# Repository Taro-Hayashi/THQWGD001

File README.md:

# 1U Wheel Encoder THQWGD001 with Tatctile Button
([日本語（note）](https://note.com/taro_hayashi/n/nf608af2136d1))

## Files
- https://github.com/Taro-Hayashi/THQWGD001/tree/main/step/THQWGD001C

<p xmlns:cc="http://creativecommons.org/ns#" xmlns:dct="http://purl.org/dc/terms/"><a property="dct:title" rel="cc:attributionURL" href="https://github.com/Taro-Hayashi/THQWGD001">THQWGD001C</a> by <a rel="cc:attributionURL dct:creator" property="cc:attributionName" href="https://x.com/w_vwbw">Taro Hayashi</a> is licensed under <a href="https://creativecommons.org/licenses/by/4.0/?ref=chooser-v1" target="_blank" rel="license noopener noreferrer" style="display:inline-block;">CC BY 4.0</a></p>

## Required

||||
|-|-|-|
|Shaft|1|THQWGD001C_shaft.stp|
|Spacer|1|THQWGD001C_spacer.stp|
|Curve wheel|1|THQWGD001C_wheel_curve.stp|
|Flat wheel|1|THQWGD001C_wheel_flat.stp|
|Base|1|THQWGD001C_base.stp|
|Cover|1|THQWGD001C_cover.stp|
|[Wheel Encoder](https://ja.aliexpress.com/item/1005010195419235.html)|1|11mm|
|[Tactile Button](https://www.aliexpress.com/w/wholesale-B3F%2525252d1062.html)|1|6x6x7mm|
|M2 screws|2|5mm or 6mm|
|M2 nuts|2||

### Assemble guide

- https://github.com/Taro-Hayashi/THQWGD001/tree/main/assemble_c.md

## Footprints and Symbol

- https://github.com/Taro-Hayashi/THQWGD001/tree/main/KiCad/

# 1U Wheel Encoder THQWGD001

## Files

- GitHub https://github.com/Taro-Hayashi/THQWGD001/tree/main/step/THQWGD001
- Printables https://www.printables.com/model/949835-1u-wheel-encoder-thqwgd001
- Maker World https://makerworld.com/en/models/550355#profileId-468693

<p xmlns:cc="http://creativecommons.org/ns#" xmlns:dct="http://purl.org/dc/terms/"><a property="dct:title" rel="cc:attributionURL" href="https://github.com/Taro-Hayashi/THQWGD001">THQWGD001</a> by <a rel="cc:attributionURL dct:creator" property="cc:attributionName" href="https://x.com/w_vwbw">Taro Hayashi</a> is licensed under <a href="https://creativecommons.org/licenses/by/4.0/?ref=chooser-v1" target="_blank" rel="license noopener noreferrer" style="display:inline-block;">CC BY 4.0</a></p>

## Required

||||
|-|-|-|
|Curve wheel|1|THQWGD001_wheel_curve.stp|
|Flat wheel|1|THQWGD001_wheel_flat.stp|
|Shaft|1|THQWGD001_shaft.stp|
|Base|1|THQWGD001_base.stp|
|Cover|1|THQWGD001_cover.stp|
|[Wheel Encoder](https://www.aliexpress.com/item/1005005353854113.html)|1|11mm|
|M2 screws|2|5mm or 6mm|
|M2 nuts|2||

### Assemble guide
- https://github.com/Taro-Hayashi/THQWGD001/tree/main/assemble.md

## Footprints and Symbol
- https://github.com/Taro-Hayashi/THQWGD001/tree/main/KiCad/

# PCB Sample
- https://github.com/Taro-Hayashi/THQWGD001/tree/main/PCB_sample

# BOOTH
https://tarohayashi.booth.pm/items/5967252

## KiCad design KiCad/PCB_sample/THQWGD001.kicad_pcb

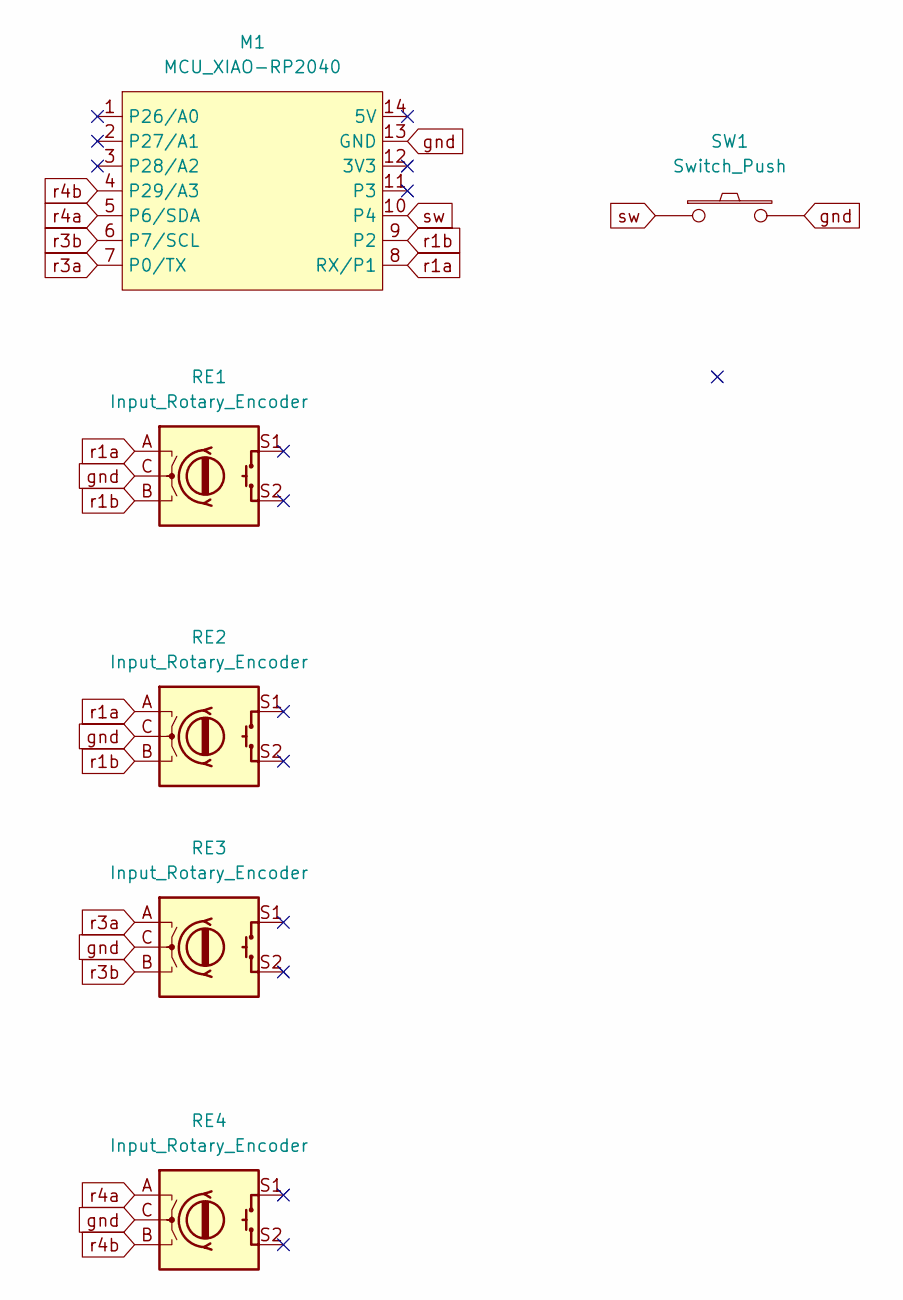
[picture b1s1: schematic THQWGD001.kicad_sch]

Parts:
M1: MCU_XIAO-RP2040; MCU_XIAO_RP2040
RE1, RE2, RE3: Input_Rotary_Encoder; THQWGD001
RE4: Input_Rotary_Encoder; THQWGD001_Reversible
SW1: Switch_Push; Switch_Cherry_MX_Socket 2

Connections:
gnd: M1.13 (GND), RE1.C, RE2.C, RE3.C, RE4.C, SW1.2
q: RE1.MP, RE2.MP
r1a: M1.8 (RX/P1), RE1.A, RE2.A
r1b: M1.9 (P2), RE1.B, RE2.B
r3a: M1.7 (P0/TX), RE3.A
r3b: M1.6 (P7/SCL), RE3.B
r4a: M1.5 (P6/SDA), RE4.A
r4b: M1.4 (P29/A3), RE4.B
sw: M1.10 (P4), SW1.1

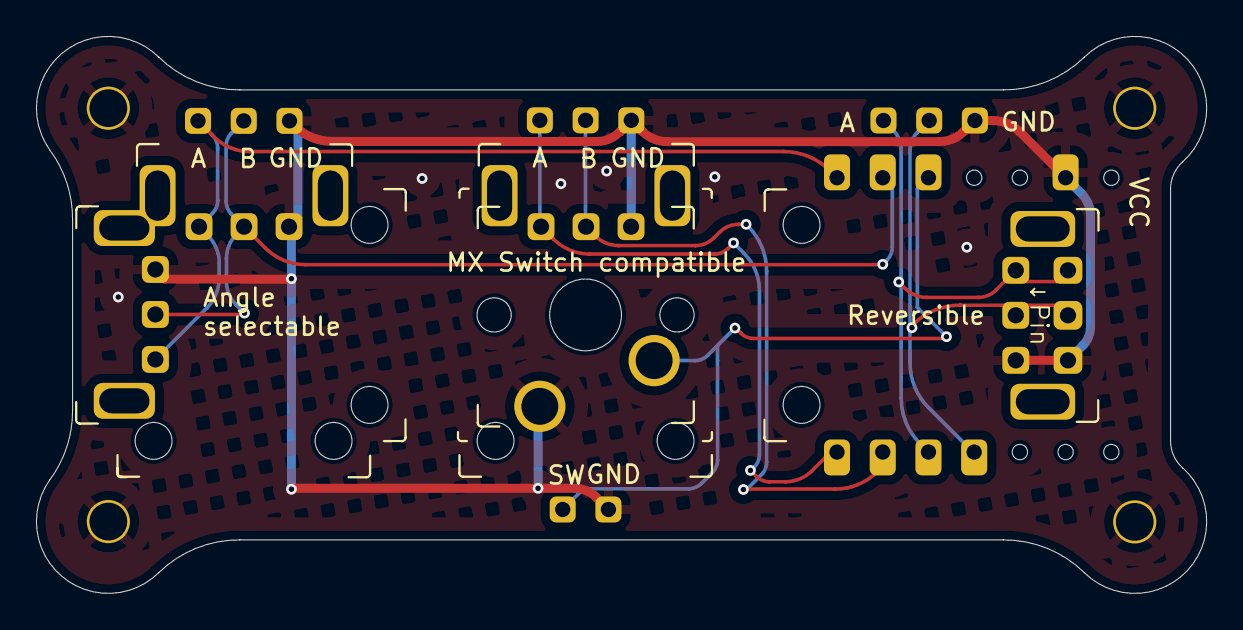
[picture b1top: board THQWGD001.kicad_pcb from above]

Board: 2 copper layers, 65.0 x 30.9 mm, 6 parts (1 on the bottom side), 9 nets.

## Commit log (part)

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2024-07-18 kicad
2024-07-21 add measurement
2024-08-16 v1.2
2024-08-28 footprint
2024-11-08 v1.3
2025-02-18 add THQWGD001C
2025-02-20 Update README.md
    I assume you have a "button", which is a sends a momentary electric impulse (and that is what AliExpress says you have in English). A 'switch' toggles from on to off to on at each click.
2025-11-03 Update link for Tactile Button in README
2025-11-13 Remove nozzle size adjustment notes from README
    Removed notes about model adjustments for nozzle size.
2025-11-13 Update README to remove clearance note
    Removed note about using THQWGD001 for side-by-side placement.
2026-01-21 Update wheel entries in README with new types
2026-05-23 fix footprints & steps
2026-05-24 test
